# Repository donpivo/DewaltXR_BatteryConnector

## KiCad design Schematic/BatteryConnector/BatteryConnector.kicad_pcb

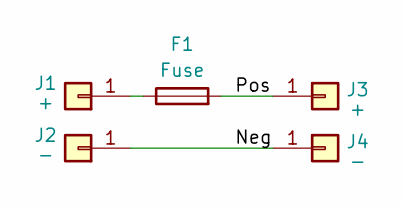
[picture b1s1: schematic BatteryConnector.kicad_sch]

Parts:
F1: Fuse; Fuse_Littelfuse_372_D8.50mm
J1: +; 62650-1
J2: -; 62650-1
J3: +; TestPoint_THTPad_D3.0mm_Drill1.5mm
J4: -; TestPoint_THTPad_D3.0mm_Drill1.5mm

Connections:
/Neg: J2.1, J4.1
/Pos: F1.2, J3.1
unnamed: F1.1, J1.1

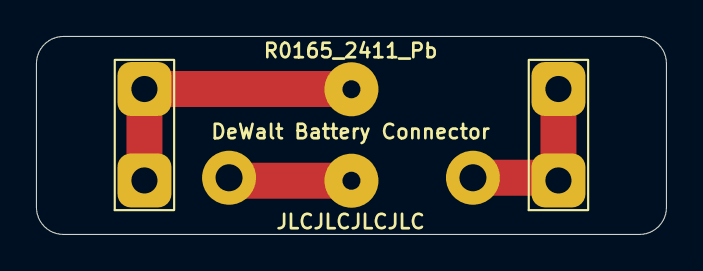
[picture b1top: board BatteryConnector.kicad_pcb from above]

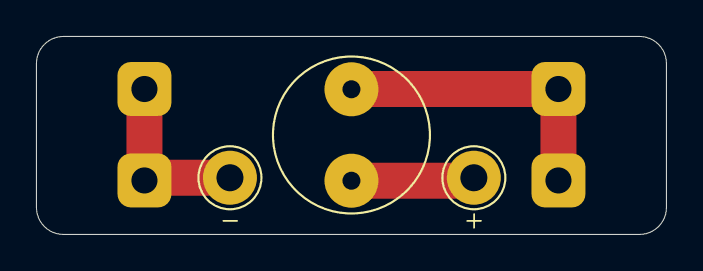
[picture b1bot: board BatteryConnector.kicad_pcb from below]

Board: 2 copper layers, 35.0 x 11.0 mm, 5 parts (3 on the bottom side), 3 nets.

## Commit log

2024-05-16 File cleanup
